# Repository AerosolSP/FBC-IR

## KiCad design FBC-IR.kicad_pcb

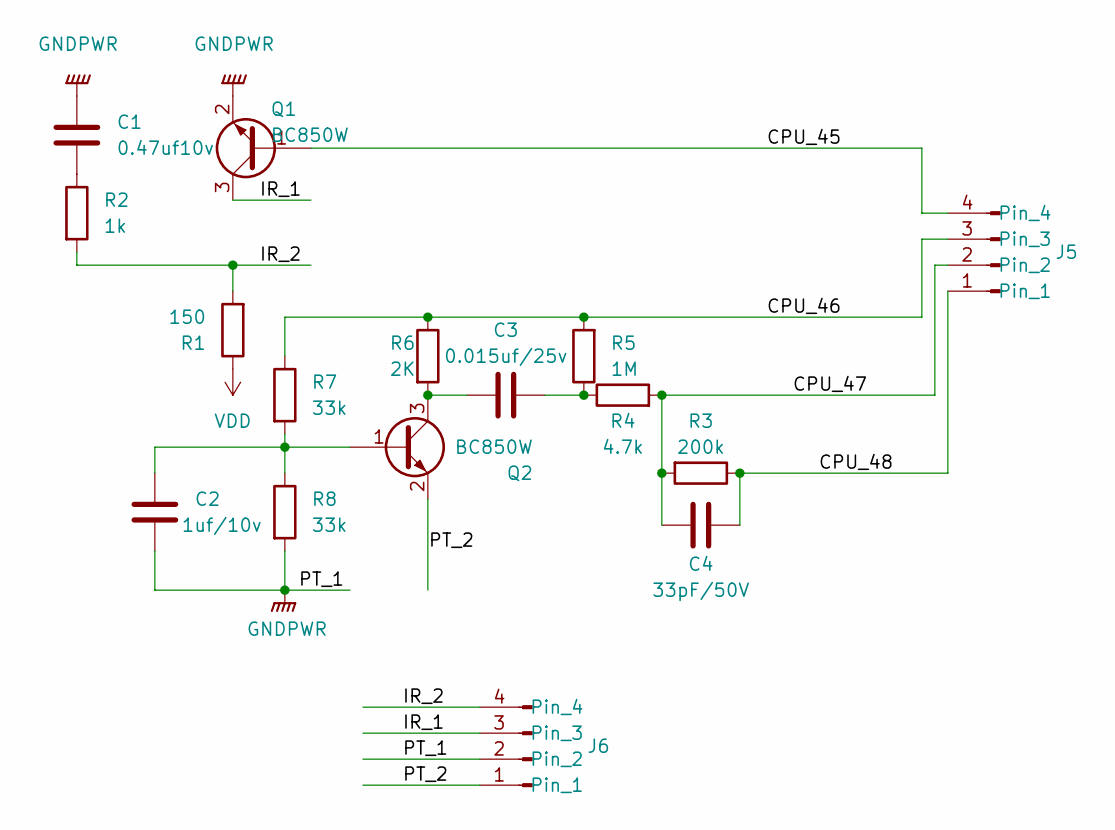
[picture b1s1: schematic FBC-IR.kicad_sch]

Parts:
C1: 0.47uf10v; C_0201_0603Metric
C2: 1uf/10v; C_0201_0603Metric
C3: 0.015uf/25v; C_0201_0603Metric
C4: 33pF/50V; C_0201_0603Metric
J5: Conn_01x04_Pin; CPU_connector
J6: Conn_01x04_Pin; LED_pad
Q1, Q2: BC850W; SOT-323_SC-70
R1: 150; R_0201_0603Metric
R2: 1k; R_0201_0603Metric
R3: 200k; R_0201_0603Metric
R4: 4.7k; R_0201_0603Metric
R5: 1M; R_0201_0603Metric
R6: 2K; R_0201_0603Metric
R7, R8: 33k; R_0201_0603Metric

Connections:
/CPU_45: J5.4, Q1.1 (B)
/CPU_46: J5.3, R5.2, R6.1, R7.1
/CPU_47: C4.1, J5.2, R3.2, R4.2
/CPU_48: C4.2, J5.1, R3.1
/IR_1: J6.3, Q1.3 (C)
/IR_2: J6.4, R1.2, R2.2
/PT_2: J6.1, Q2.2 (E)
GNDPWR: C1.1, C2.2, J6.2, Q1.2 (E), R8.2
unnamed: C1.2, R2.1
unnamed: C3.2, R4.1, R5.1
unnamed: C2.1, Q2.1 (B), R7.2, R8.1
unnamed: C3.1, Q2.3 (C), R6.2
VDD: R1.1

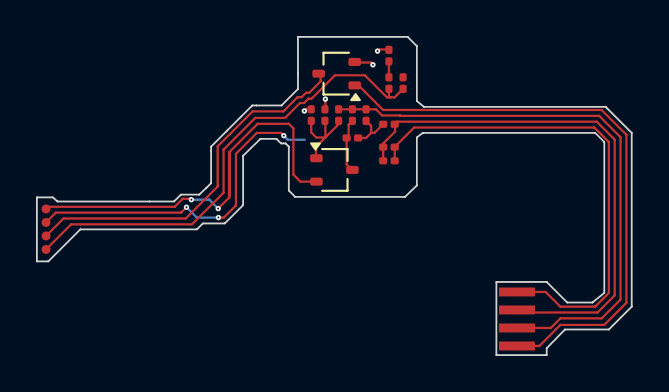
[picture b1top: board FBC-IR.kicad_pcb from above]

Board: 2 copper layers, 33.0 x 17.7 mm, 16 parts (0 on the bottom side), 12 nets.

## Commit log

2024-03-22 Add files via upload
    Initial upload
2024-03-22 Add files via upload
    Added CPU connection footprints and LED solder pad footprints
2024-03-22 Add files via upload
    Fixed CPU connectors causing DRC error. Replaced LED pads with a 1x4 footprint. Fixed Q1 and Q2 footprints not matching prior footprint due to kicad 8.0 upgrade
